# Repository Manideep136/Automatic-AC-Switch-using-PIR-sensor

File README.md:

# Automatic-AC-Switch-using-PIR-sensor

## 📌 Project Overview

The **Automatic AC Switch Using PIR Sensor** is an electronics project designed to automatically control an electrical load based on human motion detection.

The Passive Infrared (PIR) sensor detects movement within its sensing range and provides a trigger signal to a switching circuit. The switching circuit controls a relay, which can be used to switch an AC-powered load such as a lamp or other suitable appliance.

This project focuses on **schematic design, PCB layout, component placement, routing, and PCB design verification using KiCad**.

## 🎯 Objectives

- Design an automatic motion-based switching circuit.
- Interface a PIR sensor with a relay driver circuit.
- Create the circuit schematic using KiCad.
- Assign appropriate footprints to electronic components.
- Design and route a custom PCB.
- Perform Electrical Rules Check (ERC) and Design Rules Check (DRC).
- Prepare the PCB design for potential manufacturing.

## ⚙️ Working Principle

1. **Motion Detection:** The PIR sensor detects changes in infrared radiation caused by movement.
2. **Signal Output:** The sensor generates an output signal when motion is detected.
3. **Switching Control:** The sensor output activates the relay driver or switching circuit.
4. **Load Activation:** The relay contacts switch the connected AC load ON.
5. **Automatic Switching:** When motion is no longer detected, the load switches OFF according to the sensor's configured delay and circuit behavior.

### Block Diagram

```text
       Human Motion
            │
            ▼
       PIR Sensor
            │
            ▼
    Switching / Driver
         Circuit
            │
            ▼
          Relay
            │
            ▼
      AC Electrical Load
```

## 🔧 Main Components

| Component            | Function                                                    |
| -------------------- | ----------------------------------------------------------- |
| PIR sensor module    | Detects human motion                                        |
| Relay                | Switches the electrical load                                |
| Transistor or driver | Drives the relay when required                              |
| Resistors            | Provide biasing and current limiting                        |
| Diode                | Protects the driver from relay coil back-EMF, when required |
| Power supply         | Provides the required DC voltage                            |
| Terminal blocks      | Provide electrical connections                              |
| PCB                  | Holds and interconnects the components                      |

*The exact component list and values depend on the final schematic and selected PIR sensor, relay, and power supply.*

## 🖥️ Software and Tools

- **KiCad** – Schematic and PCB design
- KiCad Schematic Editor
- KiCad PCB Editor
- Footprint and symbol libraries
- 3D PCB Viewer
- Electrical Rules Check (ERC)
- Design Rules Check (DRC)

## 🧩 PCB Design Workflow

### 1. Schematic Design

The circuit schematic is created in KiCad, including the PIR sensor interface, switching circuit, relay driver, and power connections.

### 2. Footprint Assignment

Suitable footprints are assigned according to the actual component packages and datasheets.

### 3. Component Placement

Components are arranged to provide clear signal paths, practical connector access, and suitable separation between low-voltage and mains-voltage sections.

### 4. PCB Routing

Copper tracks are routed according to the schematic connections and the electrical requirements of the circuit.

### 5. Ground Plane

A GND copper zone can be added where appropriate to provide a common ground return for the low-voltage circuit.

### 6. Design Verification

ERC and DRC are used to identify electrical connection issues, clearance violations, unconnected nets, and other layout problems.

### 7. Manufacturing Preparation

Gerber and drill files can be generated after the PCB layout has been finalized and verified.

## 📐 PCB Design Considerations

- Use footprints that match the actual components.
- Check relay coil voltage and contact ratings.
- Verify the PIR sensor's operating voltage and output logic.
- Provide adequate trace widths for the intended current.
- Maintain appropriate creepage, clearance, and isolation between mains and low-voltage circuits.
- Keep high-voltage and low-voltage copper areas properly separated.
- Use connectors rated for the intended voltage and current.
- Verify the relay's contact arrangement (COM, NO, and NC) before connecting the load.

## 🔍 Design Verification Checklist

- [x] Schematic completed
- [x] Footprints verified
- [x] Component placement checked
- [x] Copper routing completed
- [x] ERC completed
- [x] DRC completed
- [x] Relay pinout verified
- [x] PCB clearances and isolation reviewed
- [x] Board outline and silkscreen checked
- [x] Gerber and drill files generated

## 📂 Suggested Repository Structure

```text
Automatic-AC-Switch-PIR/
│
├── README.md
├── Schematic/
│   └── Automatic_AC_Switch.kicad_sch
├── PCB/
│   └── Automatic_AC_Switch.kicad_pcb
├── Images/
│   ├── schematic.png
│   ├── pcb-layout.png
│   └── 3d-view.png
├── BOM/
│   └── BOM.csv
└── Gerber/
    └── Manufacturing_Files/
```

## 🚧 Project Status

| Stage                | Status                           |
| -------------------- | -------------------------------- |
| Circuit schematic    | Based on project design          |
| Footprint assignment | To be verified                   |
| PCB layout           | Based on current design progress |
| ERC/DRC              | To be completed and verified     |
| Manufacturing files  | To be generated                  |
| PCB fabrication      | Not claimed                      |
| Hardware testing     | Not claimed                      |

Update the status table to reflect the actual progress of your project before publishing it.

## 🚀 Future Improvements

- Add adjustable motion-detection delay.
- Add sensitivity adjustment, if supported by the PIR module.
- Optimize PCB size and component placement.
- Add mounting holes and clear connector labels.
- Improve enclosure integration.
- Fabricate and test the PCB under appropriate safety conditions.

## ⚠️ Safety Notice

This circuit may control **AC mains voltage, which can cause electric shock, serious injury, or fire**. Maintain appropriate isolation and mains-rated component selection. Do not handle or modify an energized circuit. Mains-side PCB design and testing should be reviewed and performed by a qualified person using suitable safety procedures. For a beginner project, consider using a certified, enclosed AC switching module or a low-voltage demonstration load.

## 📚 Learning Outcomes

This project provides practical experience with:

- Electronic schematic design
- PCB footprint selection
- Component placement and routing
- Relay-driver circuit design
- Copper zones and grounding
- ERC and DRC verification
- PCB documentation and manufacturing preparation

## 🛠️ Project Tools

**Design Software:** KiCad
**Project Type:** Electronics and PCB Design
**Application:** Motion-activated electrical switching
**Output:** Schematic, PCB layout, and optional manufacturing files

---

**Note:** This repository documents the PCB design. Fabrication and hardware testing should only be marked complete after they have actually been performed.

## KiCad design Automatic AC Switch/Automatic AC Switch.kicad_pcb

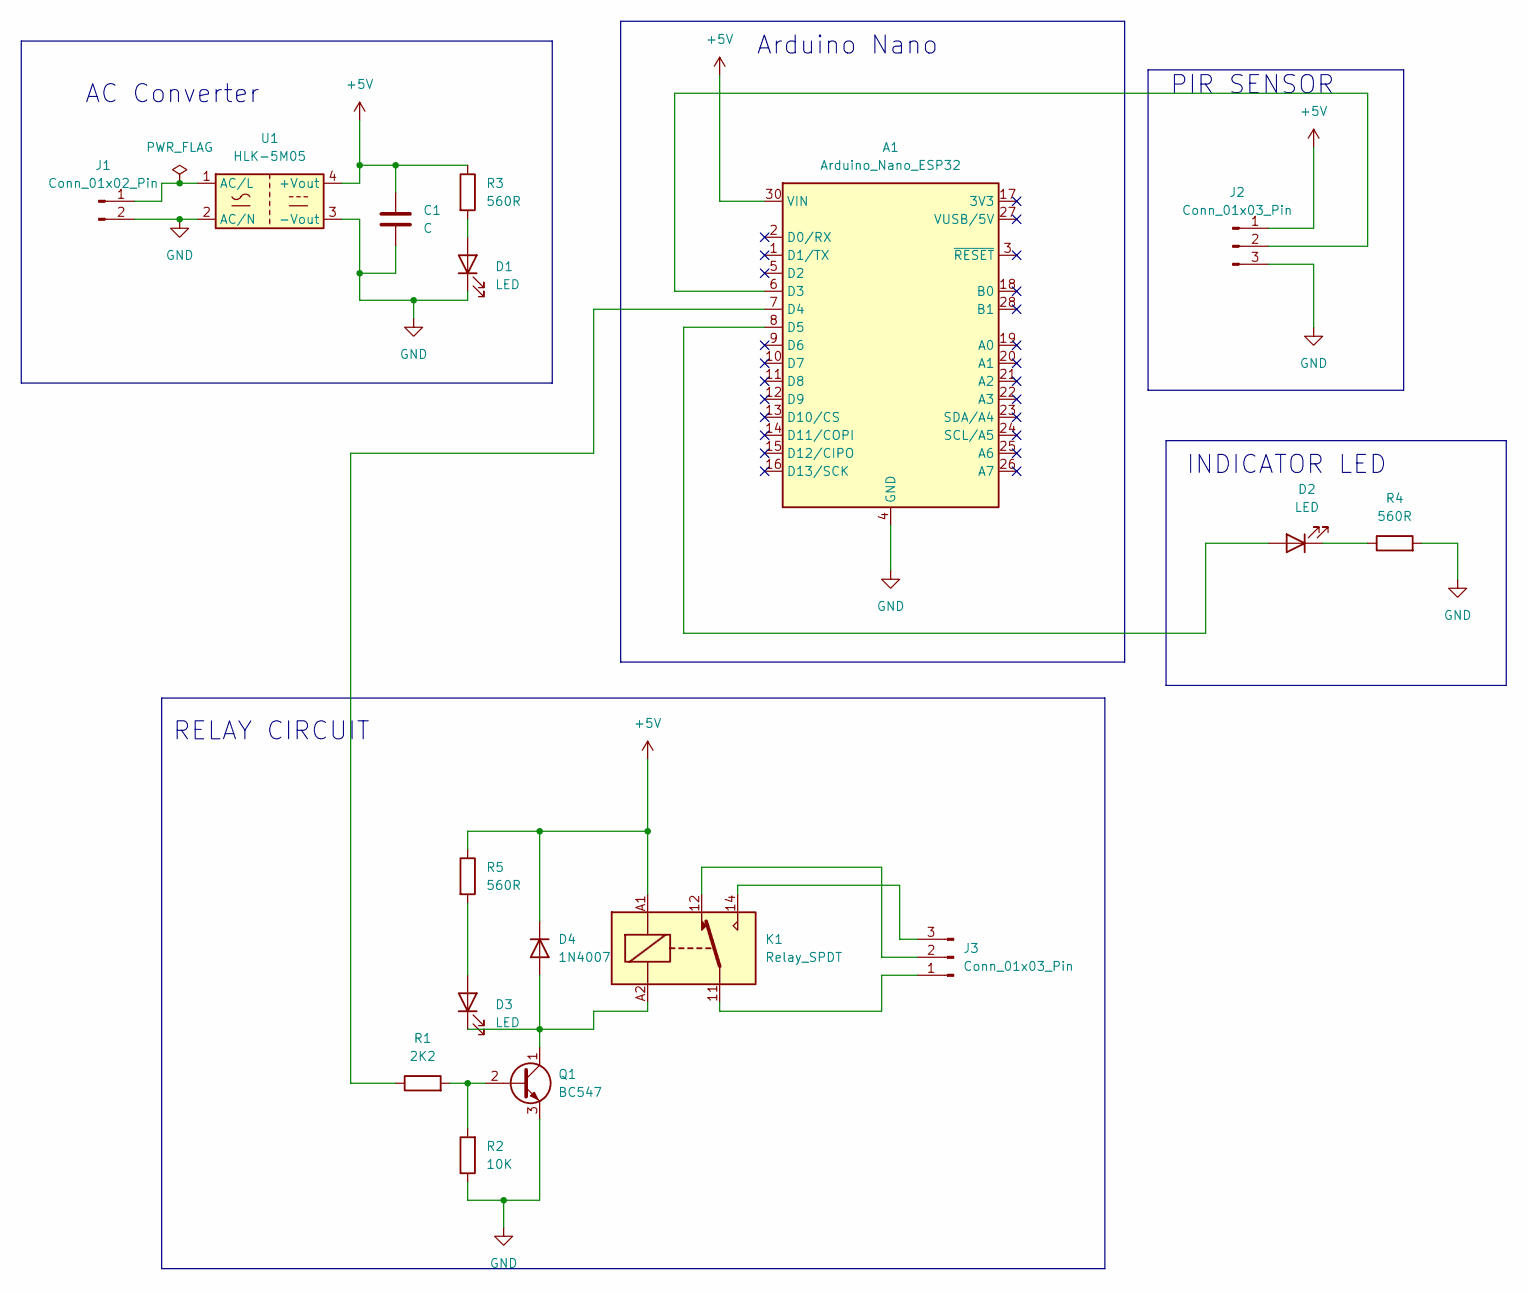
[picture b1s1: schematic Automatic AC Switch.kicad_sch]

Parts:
A1: Arduino_Nano_ESP32; Arduino_Nano
C1: C; CP_Radial_D22.0mm_P10.00mm_SnapIn
D1, D2, D3: LED; LED_D5.0mm
D4: 1N4007; D_DO-41_SOD81_P10.16mm_Horizontal
J1: Conn_01x02_Pin; TerminalBlock_Phoenix_MKDS-1,5-2_1x02_P5.00mm_Horizontal
J2: Conn_01x03_Pin; HC-SR501
J3: Conn_01x03_Pin; TerminalBlock_Phoenix_MKDS-1,5-3_1x03_P5.00mm_Horizontal
K1: Relay_SPDT; Relay_1-Form-C_Schrack-RYII_RM3.2mm
Q1: BC547; TO-92_Inline
R1: 2K2; R_Axial_DIN0309_L9.0mm_D3.2mm_P12.70mm_Horizontal
R2: 10K; R_Axial_DIN0309_L9.0mm_D3.2mm_P12.70mm_Horizontal
R3, R4, R5: 560R; R_Axial_DIN0309_L9.0mm_D3.2mm_P12.70mm_Horizontal
U1: HLK-5M05; Converter_ACDC_Hi-Link_HLK-5Mxx

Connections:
+5V: A1.30 (VIN), C1.1, D4.1 (K), J2.1, K1.A1, R3.1, R5.1, U1.4 (+Vout)
GND: A1.4 (GND), A1.29 (GND), C1.2, D1.1 (K), J1.2, J2.3, Q1.3 (E), R2.1, R4.2, U1.2 (AC/N), U1.3 (-Vout)
unnamed: A1.6 (D3), J2.2
unnamed: A1.7 (D4), R1.1
unnamed: A1.8 (D5), D2.2 (A)
unnamed: D1.2 (A), R3.2
unnamed: D2.1 (K), R4.1
unnamed: D3.2 (A), R5.2
unnamed: D3.1 (K), D4.2 (A), K1.A2, Q1.1 (C)
unnamed: J1.1, U1.1 (AC/L)
unnamed: J3.1, K1.11
unnamed: J3.2, K1.12
unnamed: J3.3, K1.14
unnamed: Q1.2 (B), R1.2, R2.2

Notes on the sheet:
RELAY CIRCUIT
PIR SENSOR
INDICATOR LED
AC Converter
Arduino Nano

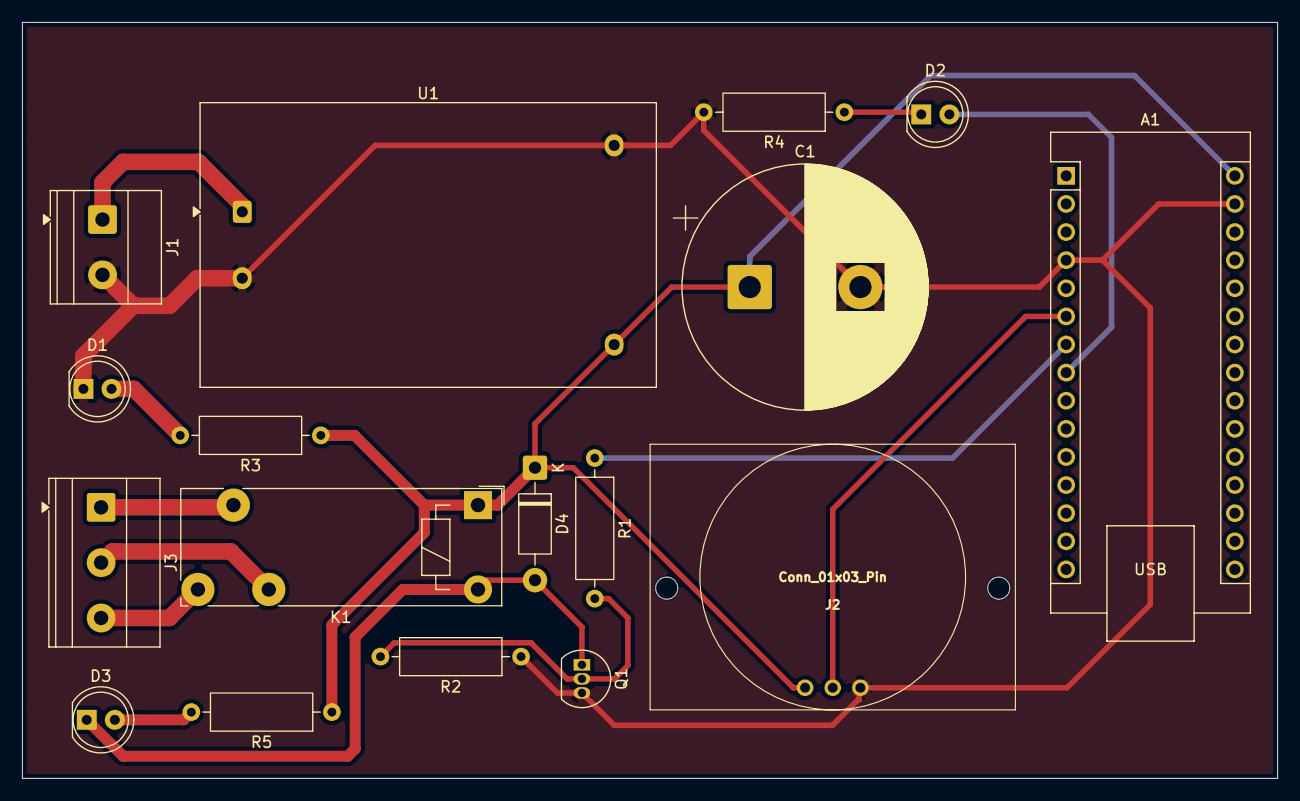
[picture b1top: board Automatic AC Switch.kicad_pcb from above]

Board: 2 copper layers, 113.4 x 68.3 mm, 17 parts (0 on the bottom side), 14 nets.
